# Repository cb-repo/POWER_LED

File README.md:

# POWER LED v1.0

POWER LED is a unique take on the traditional LED power-indicator design: originally designed for combat robotics, but it's ideal for any application requiring a small easy-to-use panel mount LED. 

Designed and built in [Christchurch, New Zealand ](https://www.google.co.nz/maps/place/Christchurch+New+Zealand) by Connor Benton, visit [cb-technology](https://www.cb-technology.co.nz/) for details.

## FEATURES

- Multiple voltage input options to suit most applications.
- Small form-factor and low-profile design allow the LED to be tucked into tighter areas that simmilar products
- Reverse-mount LED allows for flush and secure mounting in high impact environments. 
- Red LED colour chosen for its visibility.

## SPECIFICATIONS
- **Dimensions:** 14.0x7.5x1.3 mm
- **Weight:** 0.2g *excluding wires or mounting fasteners*
- **Input Voltage:** 3V3, 5V, and 12V options
- **Current Consumption:** 10mA max
- **Mounting Fasteners:** M2

## MOUNTING HOLE PATTERN 
Note: If you do not have an appropriate drill-bit for the two mounting holes, a standard 2[mm] will also work.

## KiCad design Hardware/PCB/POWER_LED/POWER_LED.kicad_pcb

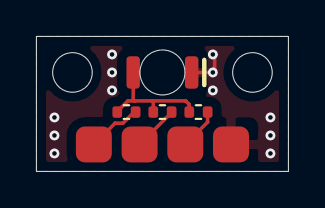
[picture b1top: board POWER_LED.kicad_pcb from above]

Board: 2 copper layers, 14.0 x 7.5 mm, 10 parts (0 on the bottom side), 5 nets.

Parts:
D1: LED; DS_Everlight_IR21-21CL110TR8
H1, H2: MountingHole; MountingHole_2.2mm_M2
H3: 12V Pad; TestPoint_Pad_2.0x2.0mm
H4: 5V Pad; TestPoint_Pad_2.0x2.0mm
H5: 3.3V Pad; TestPoint_Pad_2.0x2.0mm
H6: GND Pad; TestPoint_Pad_2.0x2.0mm
R1: 620R; R_0402
R2: 270R; R_0402
R3: 180R; R_0402

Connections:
unnamed: D1.1, H6.1
unnamed: D1.2, R1.1, R2.1, R3.1
unnamed: H3.1, R1.2
unnamed: H4.1, R2.2
unnamed: H5.1, R3.2

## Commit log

2021-10-17 v1.0 Release
2021-10-23 Sync file structure
2022-01-23 Update BOM
2022-01-25 Update assets for Readme
2022-02-19 Sync Files
2022-02-19 Updated installation instructions
2022-02-19 Updated grammar in Readme
2022-02-27 Update Latest Print Files
2022-03-20 Update Datasheet for Release
2022-06-08 GENERAL: Initialise LFS in REPO
2022-06-08 MECH: Sync Latest Revision Files
2022-07-23 Update Readme for release on CRNZ
2022-07-23 Update image format to fix display issue
2022-07-23 Update mount template image file name in readme
2024-06-04 Update Packaging Label
